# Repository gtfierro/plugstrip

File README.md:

# Plug Strip

IDD project

### Directories
* `lua/`: lua scripts for the firestorm
* `nodeapp/`: quick nodejs app for sending 0/1 to a firestorm using UDP/IPv6
* `eagle/`: directory for Eagle-related parts of the project
    * `libraries/`: part libraries (probably custom ones)

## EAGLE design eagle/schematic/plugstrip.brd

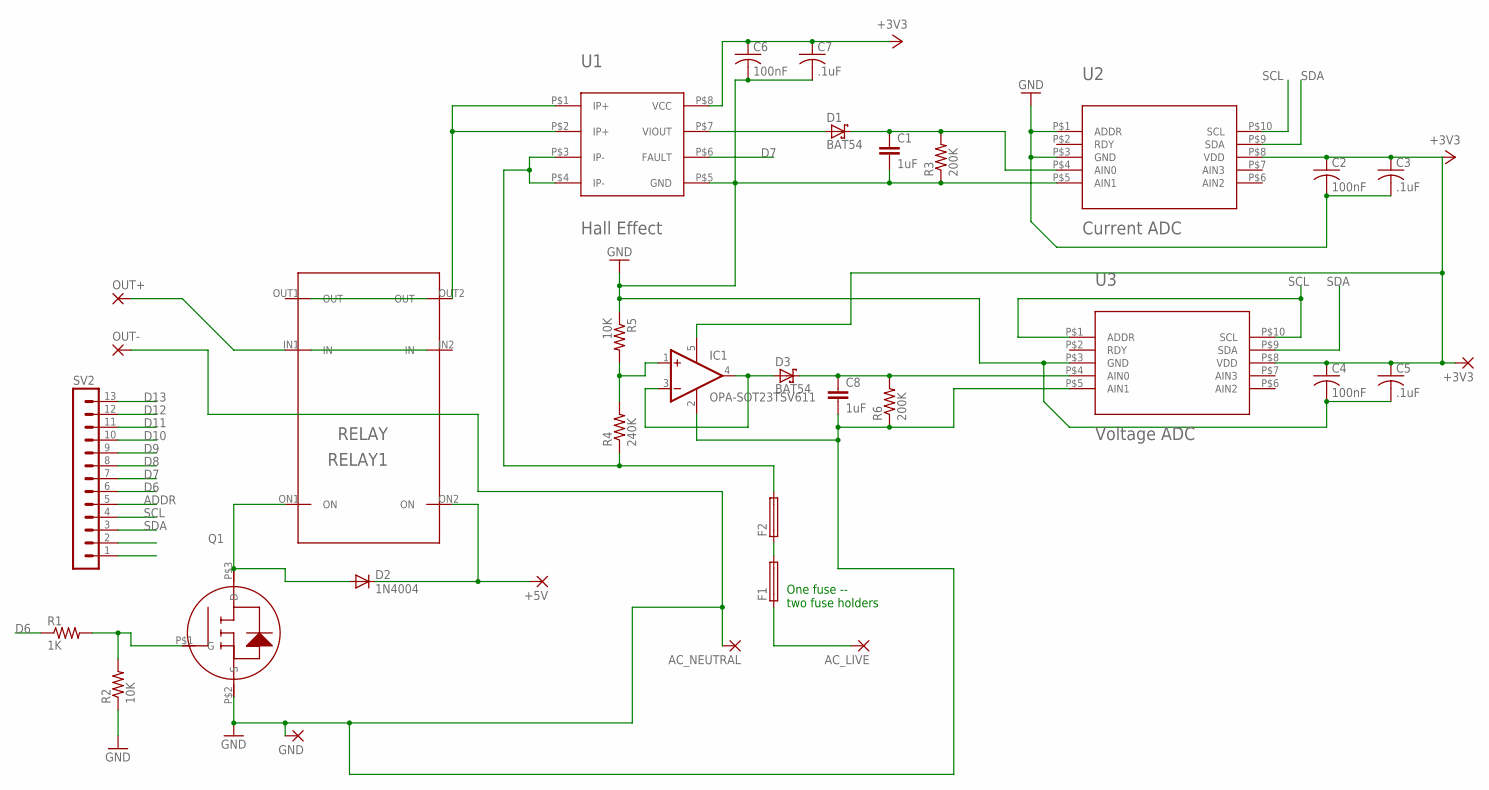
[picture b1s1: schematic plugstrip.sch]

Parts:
+3V3, +5V: 3,81/1,4
AC_LIVE: 3,81/1,4
AC_NEUTRAL: 3,81/1,4
C1, C8: 1uF; C2.5-2
C2, C4, C6: 100nF; C1206
C3, C5, C7: .1uF; C1206
D1, D3: BAT54; SOT23
D2: 1N4004; DO41-10
F1, F2: 19560
GND: 3,81/1,4
IC1: OPA-SOT23TSV611; SOT23-5
OUT+: 3,81/1,4
OUT-: 3,81/1,4
Q1: BSH105; SOT23
R1: 1K; 0411/15
R2, R5: 10K; 0411/15
R3, R6: 200K; 0411/15
R4: 240K; 0411/15
RELAY1: RELAY; G5RL-1A-E-HR
SV2: MA13-1
U1: Hall Effect; ACS711
U2: Current ADC; ADS1013
U3: Voltage ADC; ADS1013

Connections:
+3V3: +3V3.1, C2.1, C3.1, C4.1, C5.1, C6.1, C7.1, IC1.5 (V+), U1.P$8 (VCC), U2.P$8 (VDD), U3.P$8 (VDD)
AC_LIVE: F2.2, R4.1, U1.P$3 (IP-), U1.P$4 (IP-)
ADDR: SV2.5
D6: R1.1, SV2.6
D7: SV2.7, U1.P$6 (FAULT)
D8: SV2.8
D9: SV2.9
D10: SV2.10
D11: SV2.11
D12: SV2.12
D13: SV2.13
GND: AC_NEUTRAL.1, C1.2, C2.2, C3.2, C4.2, C5.2, C6.2, C7.2, C8.2, GND.1, IC1.2 (V-), OUT-.1, Q1.P$2 (S), R2.1, R3.1, R5.1, R6.1, U1.P$5 (GND), U2.P$1 (ADDR), U2.P$3 (GND), U2.P$5 (AIN1), U3.P$3 (GND), U3.P$5 (AIN1)
unnamed: OUT+.1, RELAY1.IN1 (IN)
unnamed: F1.2, F2.1
unnamed: D2.A, Q1.P$3 (D), RELAY1.ON1 (ON)
unnamed: C1.1, D1.3 (C), R3.2, U2.P$4 (AIN0)
unnamed: Q1.P$1 (G), R1.2, R2.2
unnamed: D1.1 (A), U1.P$7 (VIOUT)
unnamed: +5V.1, D2.C, RELAY1.ON2 (ON)
unnamed: RELAY1.OUT2 (OUT), U1.P$1 (IP+), U1.P$2 (IP+)
unnamed: AC_LIVE.1, F1.1
unnamed: C8.1, D3.3 (C), R6.2, U3.P$4 (AIN0)
unnamed: D3.1 (A), IC1.3 (-IN), IC1.4 (OUT)
unnamed: IC1.1 (+IN), R4.2, R5.2
SCL: SV2.4, U2.P$10 (SCL), U3.P$1 (ADDR), U3.P$10 (SCL)
SDA: SV2.3, U2.P$9 (SDA), U3.P$9 (SDA)

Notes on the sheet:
One fuse -- two fuse holders

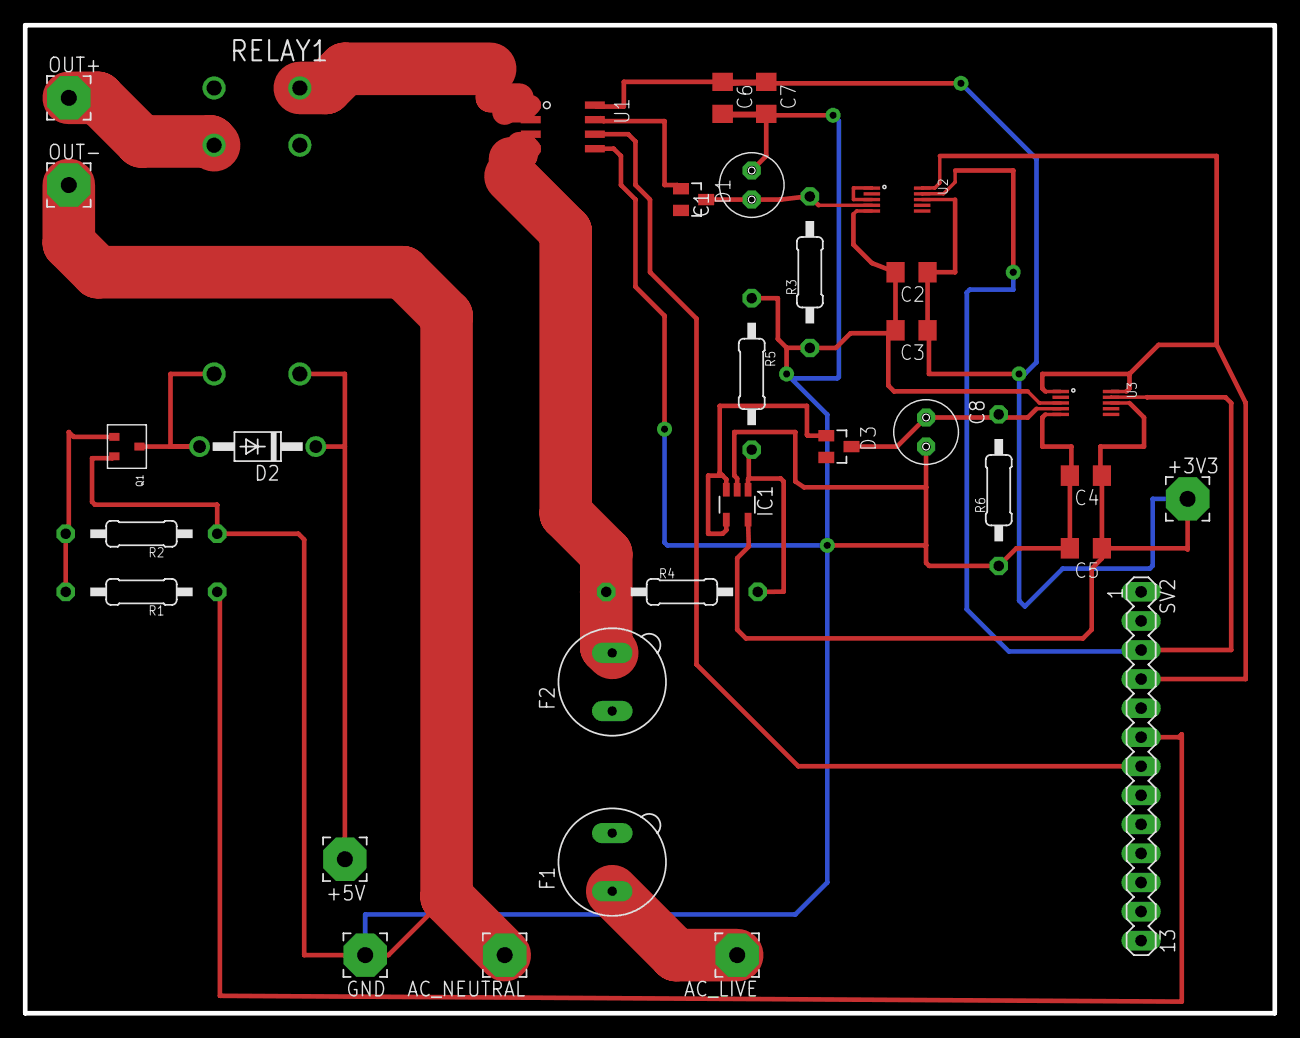
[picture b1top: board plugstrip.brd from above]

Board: 2 copper layers, 109.2 x 86.4 mm, 33 parts (0 on the bottom side), 19 nets.

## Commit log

2015-11-03 add nodeapp
2015-11-03 commit stuff
2015-11-03 add ADS1013 IDGST part
2015-11-03 update directory listing to include eagle
2015-11-03 add acs711 hall effect
2015-11-04 add G5RL-1A-E-HR relay
2015-11-04 add Eagle library with resistors, capacitor, and mosfet
2015-11-04 Edits to the libraries
2015-11-04 add plugstrip schematic beginning
2015-11-04 add unmodified board
2015-11-04 update board
2015-11-04 add labels to the relay
2015-11-04 save schematic, board
2015-11-05 add react-native plugstriproject
2015-11-05 start basic app
2015-11-06 continuing along with android app
2015-11-06 Added voltage measurement circuitry
2015-11-07 BLE almost works
2015-11-07 BLE scan page works!
2015-11-07 fix back buttons
2015-11-08 starting to scan, connect, look at GATT
2015-11-08 starting header
2015-11-08 some styling on BLE scan results
2015-11-09 First cut at web application; no scheduling yet
2015-11-09 Progress on webapp UI and some scheduling logic
2015-11-09 update server
2015-11-09 more gatt scanning
2015-11-09 bug fixes, disconnecting automatically
2015-11-09 Avoid null pointer on closing BLE device when not connected
2015-11-09 Better button styling for BLE GATT
2015-11-09 better buttons, more state
2015-11-10 Removed hardcoding from web app, implemented remote actuation from web interface for plug details, implemented on-demand permalink generation
2015-11-10 adjustments on schematic
2015-11-11 more schematic?
2015-11-11 update schematic
2015-11-12 more layout
2015-11-12 add fuse, remove ground routing
2015-11-12 add the stuff
2015-11-13 layout!
2015-11-16 update board layout
2015-11-16 add gerber files
2015-11-19 Implement creation of scheduled actuation events
2015-11-21 Implemented actuation event deletion -- both back and front ends
2015-11-22 Add some error handling and documentation for scheduling API
2015-11-24 add readme
2015-11-24 Add in configuration for BLE plugstrip
2015-11-24 Fix back command, configure button styling
2015-11-24 Remove extra plugs, read correctly from state on connect
2015-11-24 send state, not a string, on connection
2015-11-24 Generate UUID from device address
    We use a UUIDv3 to create a consistent hashing from the device's address
    (MAC-like) to the base UUID for this source.
2015-11-24 advertise 154 mac adress in 0xb00e characteristic
2015-11-24 Read 154 mac addr from characteristic in android app
2015-11-25 Improve error handling in web app
2015-11-25 generate uuidv3 in java
2015-11-25 Rough draft of ADC code for FireStorm
2015-11-30 Add very simple but functional Lua code to read from current ADC
2015-11-30 add enclosure
2015-11-30 notify BLE on state change
2015-11-30 update parts: plug receptacle now 25mm
2015-11-30 fix up smap forwarding
2015-11-30 wakka wakka
2015-11-30 Change Webapp's use of metadata to accommodate configuration
2015-11-30 Use MAC address to store metadata so it persists across prefix changes
2015-11-30 Clean up schedule formatting on UI, change plotter permalinks to autoscale Y axis
2015-12-02 Display current state on plugstrip web page
2015-12-02 Add hour, day and week plots to plugstrip webpage and improve its layout
2015-12-05 fix buttons
2015-12-05 add progress HUD for scanning
2015-12-05 do not change screen on scan fail
2015-12-06 fix BLE scan in android 6.0
2015-12-06 filter out non-plugstrips from BLE scan results, add write retries
2015-12-06 Uncomment I2C comms since both ADCs are now working
2015-12-06 Fixed webapp so it actually returns 404 when plugstrip not found
2015-12-06 Added sanity checks for event scheduling parameters
2015-12-07 add instructions for the lack of being able to request location permissions
2015-12-07 dumbest reliable write protocol ever
2015-12-07 so pretteh
2015-12-07 add view config page
2015-12-08 Add basic form validation for actuation scheduling
2015-12-09 Print more information about I2C comms
2015-12-10 use some global vars to get it to work
2015-12-10 Change web app to use Metadata/Plugstrip instead of power stream UUID as primary identifier
2015-12-10 Fix annoying JavaScript interface issue on plugstrip page
2015-12-10 Fixed timezone issue
2015-12-15 best fix
2015-12-15 update the smapforward script
2016-01-29 add plugshield schematic
2016-01-29 changes to app
2016-01-29 add gerber for plugshield
